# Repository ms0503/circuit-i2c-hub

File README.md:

レベル変換付きI²Cハブ
=============

レベル変換付きI²Cハブはプルアップ切り替え機能、
スレーブ側の信号レベル・供給電圧を3.3V・5Vから選択する機能を備えた5口I²Cハブです。
基本的にマスター側からの5V供給で動きますが外部電源からの供給も可能です。

# インターフェース
## マスター
電源ラインは5V固定、信号レベルは3.3V固定です。外部電源未接続時の電源供給も兼務しています。
横のスイッチでプルアップの切り替えを行うことができます。

## スレーブ
電源ライン・信号レベルは3.3V・5Vから選択でき、横のスイッチでプルアップの切り替えを行うことができます。
4つ搭載されています。

# ライブラリ
この基板は一部のシンボル・フットプリントに[kicad-mecha](https://github.com/ms0503/kicad-mecha.git)を使用しています。
別途インポートした上でご利用下さい。

# 設計者
Sora Tonami <[ms0503@outlook.com](mailto:ms0503@outlook.com)>

# ライセンス
この基板のデータは[MITライセンス](LICENSE.md)の下に公開されます。ご自由に改変・再配布して頂いて構いません。

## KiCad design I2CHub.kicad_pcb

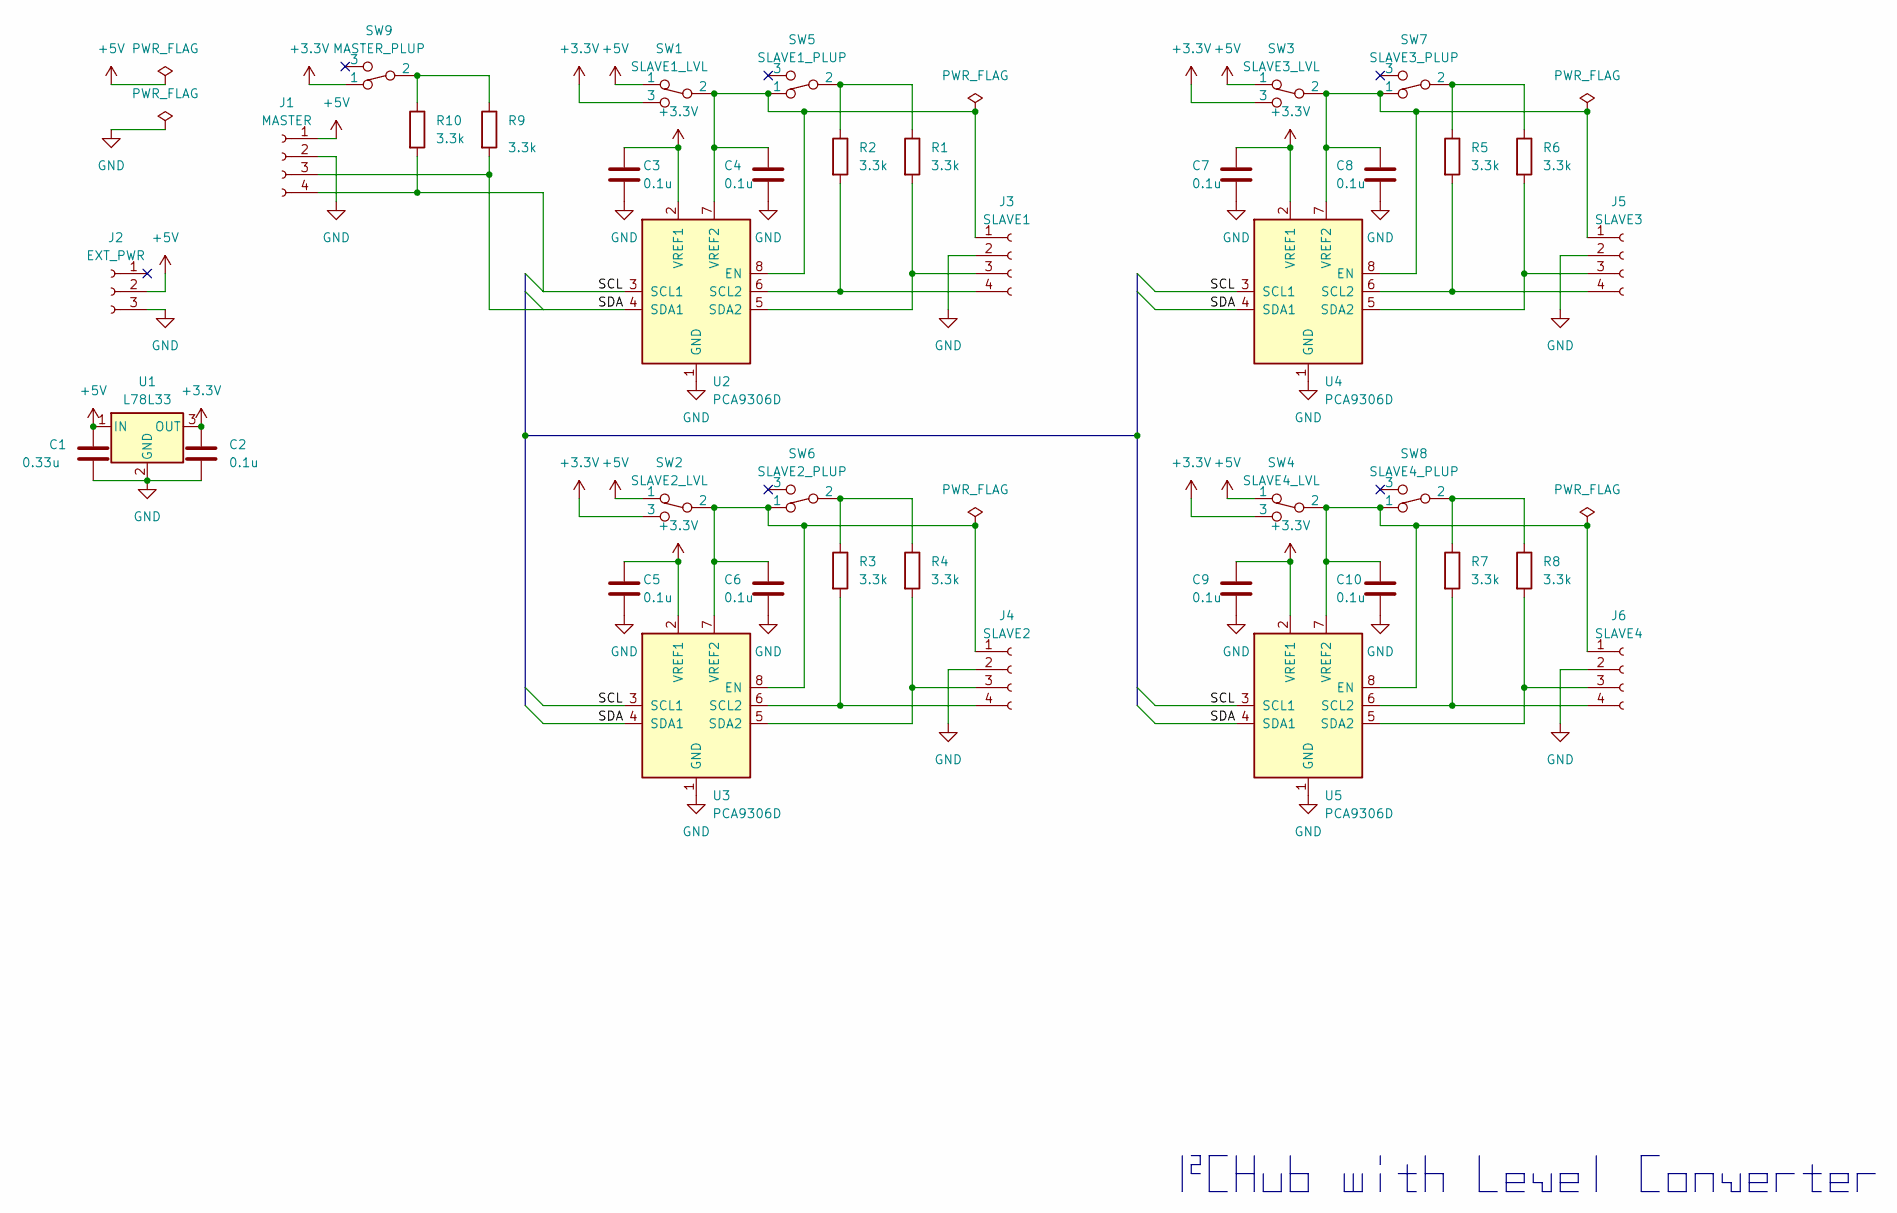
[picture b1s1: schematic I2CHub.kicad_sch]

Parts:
C1: 0.33u; C_0805_2012Metric
C2, C3, C4, C5, C6, C7, C8, C9, C10: 0.1u; C_0805_2012Metric
J1: MASTER; XA_4pin_Straight
J2: EXT_PWR; JST_XH_B3B-XH-A_1x03_P2.50mm_Vertical
J3: SLAVE1; XA_4pin_Straight
J4: SLAVE2; XA_4pin_Straight
J5: SLAVE3; XA_4pin_Straight
J6: SLAVE4; XA_4pin_Straight
R1, R2, R3, R4, R5, R6, R7, R8, R9, R10: 3.3k; R_0603_1608Metric
SW1: SLAVE1_LVL; toggle_1-2
SW2: SLAVE2_LVL; toggle_1-2
SW3: SLAVE3_LVL; toggle_1-2
SW4: SLAVE4_LVL; toggle_1-2
SW5: SLAVE1_PLUP; toggle_1-2
SW6: SLAVE2_PLUP; toggle_1-2
SW7: SLAVE3_PLUP; toggle_1-2
SW8: SLAVE4_PLUP; toggle_1-2
SW9: MASTER_PLUP; toggle_1-2
U1: L78L33; SOT-89-3
U2, U3, U4, U5: PCA9306D; SO-8_3.9x4.9mm_P1.27mm

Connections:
+3.3V: C2.1, C3.1, C5.1, C7.1, C9.1, SW1.3, SW2.3, SW3.3, SW4.3, SW9.1, U1.3 (OUT), U2.2 (VREF1), U3.2 (VREF1), U4.2 (VREF1), U5.2 (VREF1)
+5V: C1.1, J1.1, J2.2, SW1.1, SW2.1, SW3.1, SW4.1, U1.1 (IN)
/SCL: J1.4, R10.2, U2.3 (SCL1), U3.3 (SCL1), U4.3 (SCL1), U5.3 (SCL1)
/SDA: J1.3, R9.2, U2.4 (SDA1), U3.4 (SDA1), U4.4 (SDA1), U5.4 (SDA1)
GND: C1.2, C2.2, C3.2, C4.2, C5.2, C6.2, C7.2, C8.2, C9.2, C10.2, J1.2, J2.3, J3.2, J4.2, J5.2, J6.2, U1.2 (GND), U2.1 (GND), U3.1 (GND), U4.1 (GND), U5.1 (GND)
unnamed: C4.1, J3.1, SW1.2, SW5.1, U2.7 (VREF2), U2.8 (EN)
unnamed: J3.3, R1.2, U2.5 (SDA2)
unnamed: J3.4, R2.2, U2.6 (SCL2)
unnamed: C6.1, J4.1, SW2.2, SW6.1, U3.7 (VREF2), U3.8 (EN)
unnamed: J4.3, R4.2, U3.5 (SDA2)
unnamed: J4.4, R3.2, U3.6 (SCL2)
unnamed: C8.1, J5.1, SW3.2, SW7.1, U4.7 (VREF2), U4.8 (EN)
unnamed: J5.3, R6.2, U4.5 (SDA2)
unnamed: J5.4, R5.2, U4.6 (SCL2)
unnamed: C10.1, J6.1, SW4.2, SW8.1, U5.7 (VREF2), U5.8 (EN)
unnamed: J6.3, R8.2, U5.5 (SDA2)
unnamed: J6.4, R7.2, U5.6 (SCL2)
unnamed: R1.1, R2.1, SW5.2
unnamed: R3.1, R4.1, SW6.2
unnamed: R5.1, R6.1, SW7.2
unnamed: R7.1, R8.1, SW8.2
unnamed: R9.1, R10.1, SW9.2

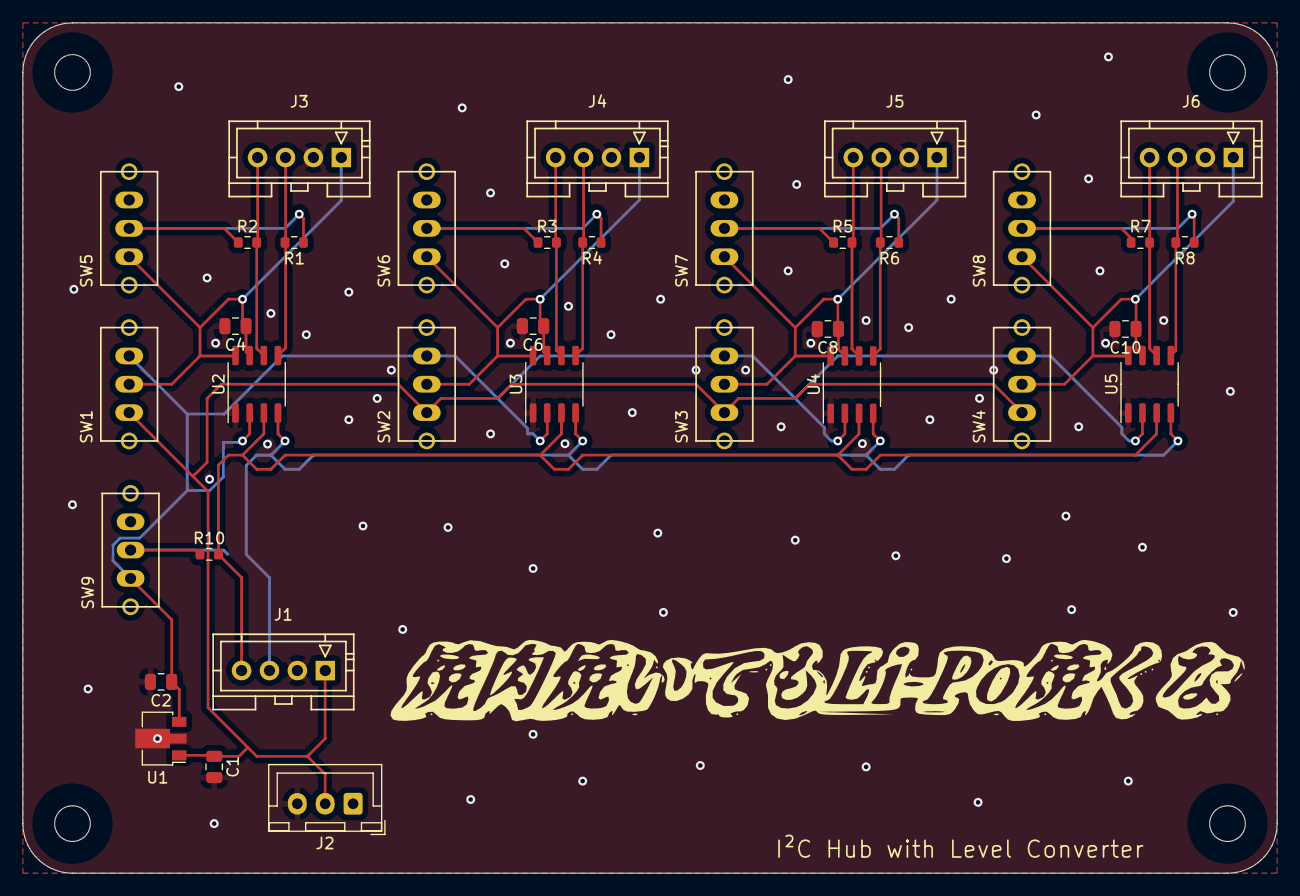
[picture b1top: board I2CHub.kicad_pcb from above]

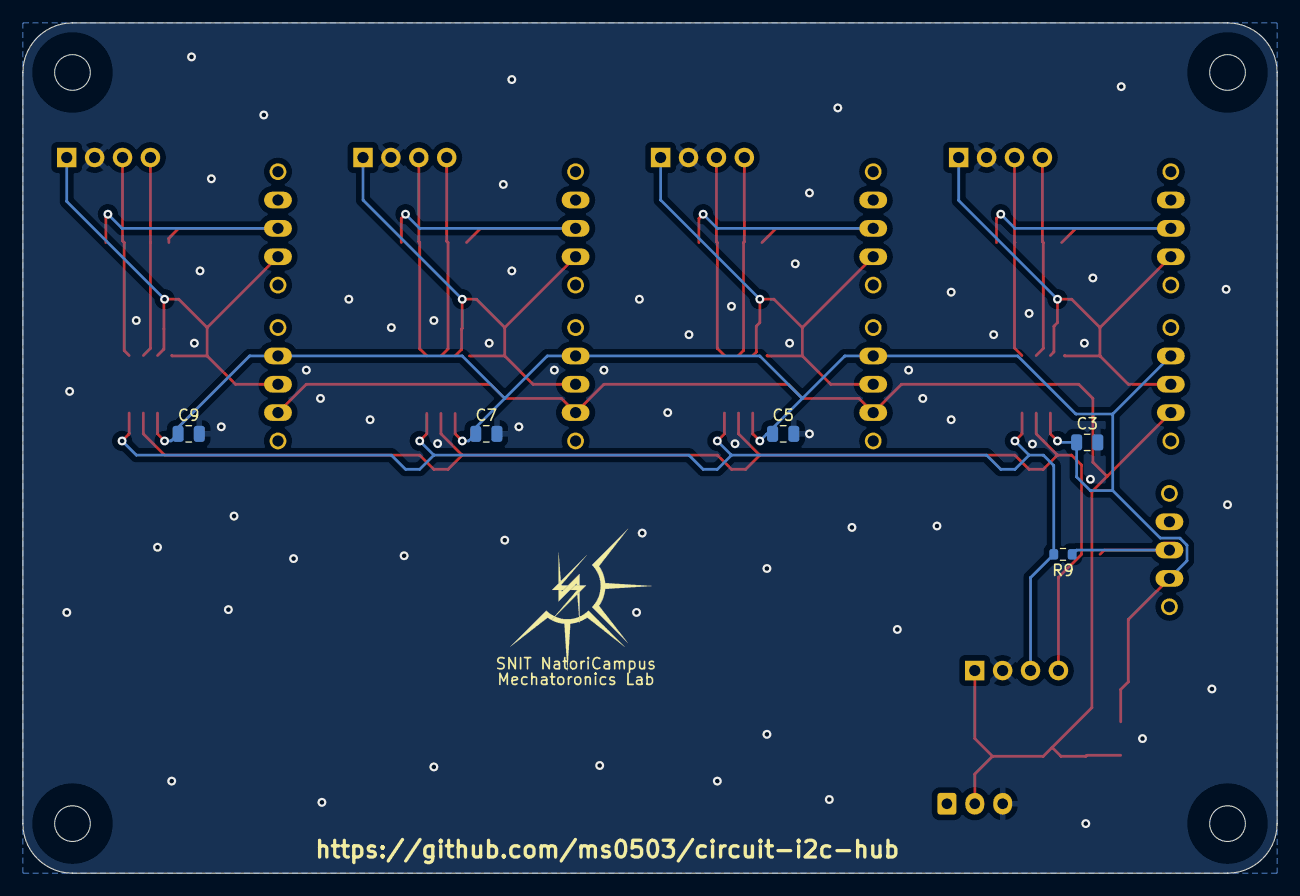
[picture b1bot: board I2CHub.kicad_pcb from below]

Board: 2 copper layers, 112.4 x 76.2 mm, 44 parts (5 on the bottom side), 22 nets.

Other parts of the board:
 : holeφ3.2
 #2,  #3,  #4: holeφ3.2
